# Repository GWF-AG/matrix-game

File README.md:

# Matrix-Game

Copyright (C) 2025 GWF AG, Obergrundstrasse 119, 6002 Lucerne, Switzerland

Contact: info@gwf.ch

## Trial Apprenticeship

This PCB is used as part of the trial apprenticeship for electronics/firmware at GWF AG in Lucerne.

_Deutsch: Schnupperlehre Elektroniker/in EFZ_

## Project

The project is used to practice soldering, measuring and potentially some coding.

The firmware currently supports the following games:
- [x] Snake
- [x] Tic-Tac-Toe
- [x] Drawing
- [x] Bomb Dodging
- [ ] Breakout

Feel free to submit a Pull Request to add more games! :tada:

## Changelogs

The changelogs can be find in the corresponding subdirectories:
- [Firmware Changelog](firmware/CHANGELOG.md)
- [Hardware Changelog](hardware/CHANGELOG.md)

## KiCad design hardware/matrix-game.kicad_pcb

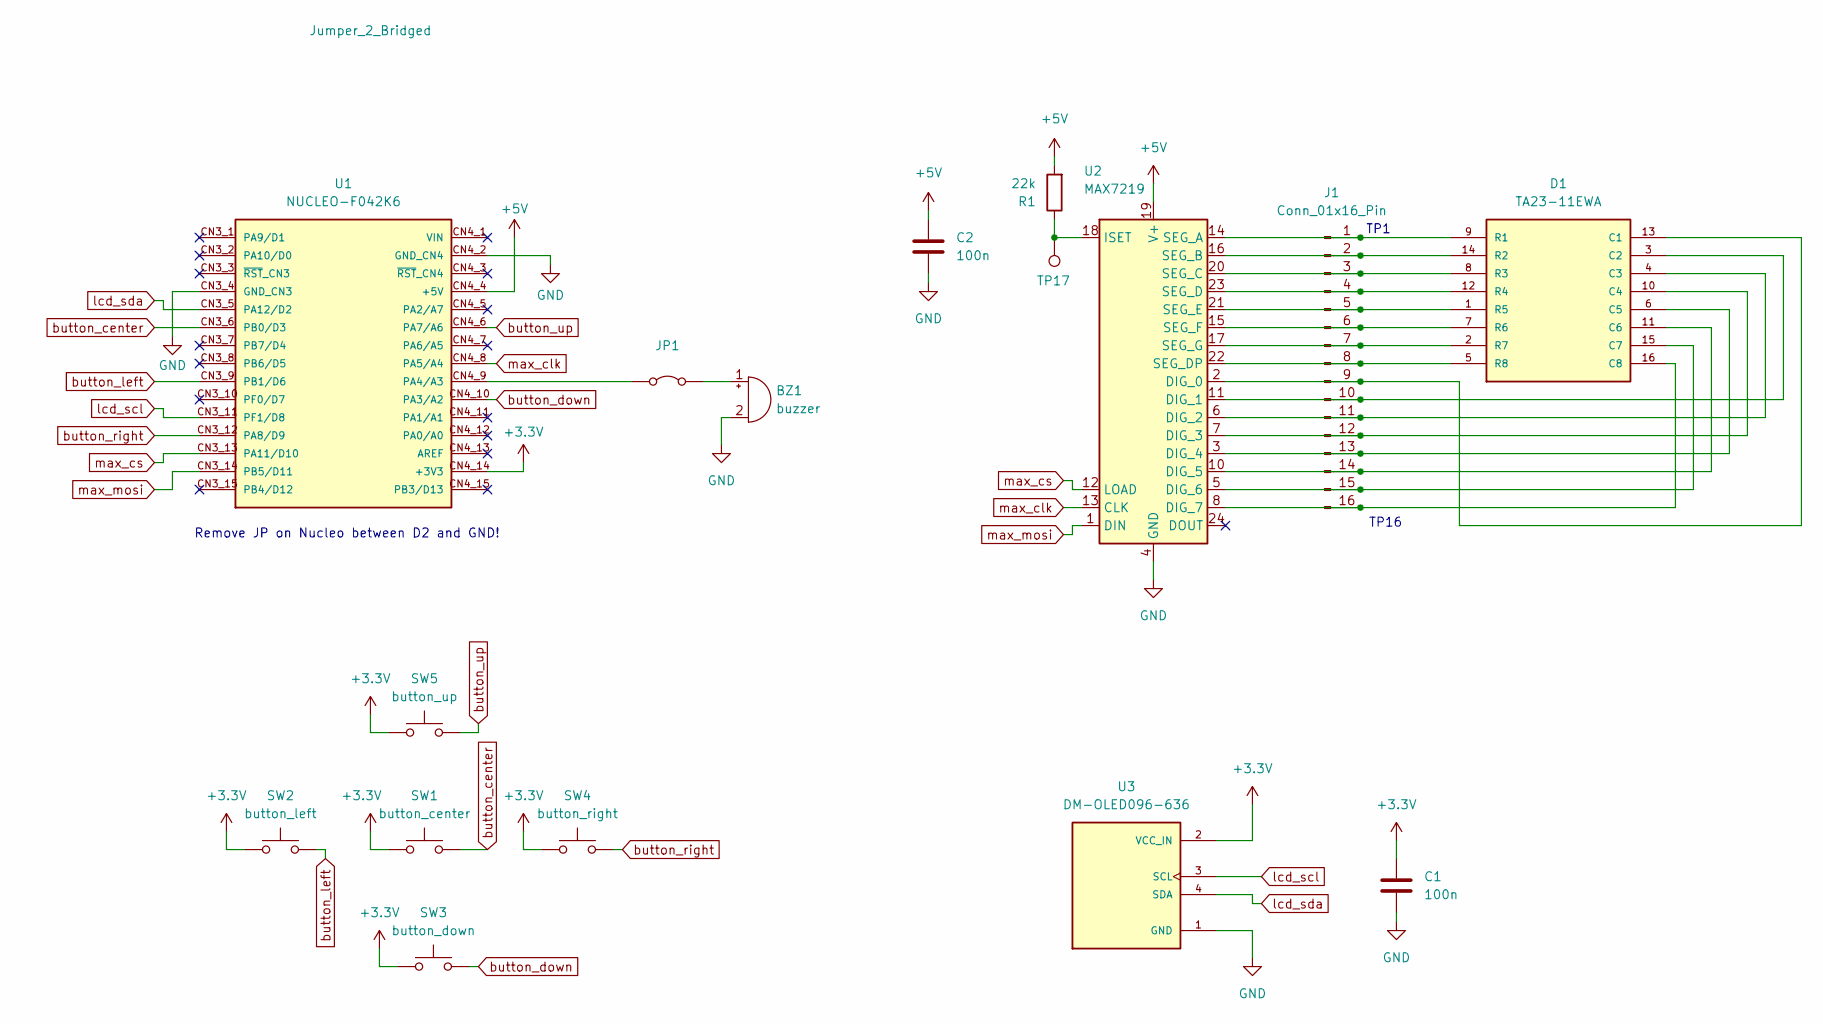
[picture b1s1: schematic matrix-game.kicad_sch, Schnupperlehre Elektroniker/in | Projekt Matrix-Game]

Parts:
BZ1: buzzer; Buzzer_12x9.5RM7.6
C1, C2: 100n; C_Disc_D3.0mm_W2.0mm_P2.50mm
D1: TA23-11EWA; LED_TA23-11EWA; PARTREV V.10A
J1: Conn_01x16_Pin; PinHeader_1x16_P2.54mm_Vertical
JP1: Jumper_2_Bridged; PinHeader_1x02_P2.54mm_Vertical
R1: 22k; R_Axial_DIN0207_L6.3mm_D2.5mm_P10.16mm_Horizontal
SW1: button_center; SW_PUSH_6mm
SW2: button_left; SW_PUSH_6mm
SW3: button_down; SW_PUSH_6mm
SW4: button_right; SW_PUSH_6mm
SW5: button_up; SW_PUSH_6mm
TP17: TestPoint; PinHeader_1x01_P2.54mm_Vertical
U1: NUCLEO-F042K6; MODULE_NUCLEO-F042K6; PARTREV 8
U2: MAX7219; DIP-24_W7.62mm_Socket
U3: DM-OLED096-636; MODULE_DM-OLED096-636; PARTREV 2018-09-10

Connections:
+3.3V: C1.1, SW1.1, SW2.1, SW3.1, SW4.1, SW5.1, U1.CN4_14 (+3V3), U3.2 (VCC_IN)
+5V: C2.1, R1.2, U1.CN4_4 (+5V), U2.19 (V+)
GND: BZ1.2 (-), C1.2, C2.2, U1.CN3_4 (GND_CN3), U1.CN4_2 (GND_CN4), U2.4 (GND), U2.9 (GND), U3.1 (GND)
unnamed: BZ1.1 (+), JP1.2 (B)
unnamed: D1.13 (C1), J1.9, U2.2 (DIG_0)
unnamed: D1.3 (C2), J1.10, U2.11 (DIG_1)
unnamed: D1.4 (C3), J1.11, U2.6 (DIG_2)
unnamed: D1.10 (C4), J1.12, U2.7 (DIG_3)
unnamed: D1.6 (C5), J1.13, U2.3 (DIG_4)
unnamed: D1.11 (C6), J1.14, U2.10 (DIG_5)
unnamed: D1.15 (C7), J1.15, U2.5 (DIG_6)
unnamed: D1.16 (C8), J1.16, U2.8 (DIG_7)
unnamed: D1.9 (R1), J1.1, U2.14 (SEG_A)
unnamed: D1.14 (R2), J1.2, U2.16 (SEG_B)
unnamed: D1.8 (R3), J1.3, U2.20 (SEG_C)
unnamed: D1.12 (R4), J1.4, U2.23 (SEG_D)
unnamed: D1.1 (R5), J1.5, U2.21 (SEG_E)
unnamed: D1.7 (R6), J1.6, U2.15 (SEG_F)
unnamed: D1.2 (R7), J1.7, U2.17 (SEG_G)
unnamed: D1.5 (R8), J1.8, U2.22 (SEG_DP)
unnamed: JP1.1 (A), U1.CN4_9 (PA4/A3)
unnamed: R1.1, TP17.1, U2.18 (ISET)
button_center: SW1.2, U1.CN3_6 (PB0/D3)
button_down: SW3.2, U1.CN4_10 (PA3/A2)
button_left: SW2.2, U1.CN3_9 (PB1/D6)
button_right: SW4.2, U1.CN3_12 (PA8/D9)
button_up: SW5.2, U1.CN4_6 (PA7/A6)
lcd_scl: U1.CN3_11 (PF1/D8), U3.3 (SCL)
lcd_sda: U1.CN3_5 (PA12/D2), U3.4 (SDA)
max_clk: U1.CN4_8 (PA5/A4), U2.13 (CLK)
max_cs: U1.CN3_13 (PA11/D10), U2.12 (LOAD)
max_mosi: U1.CN3_14 (PB5/D11), U2.1 (DIN)

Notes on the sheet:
TP16
TP1
Remove JP on Nucleo between D2 and GND!

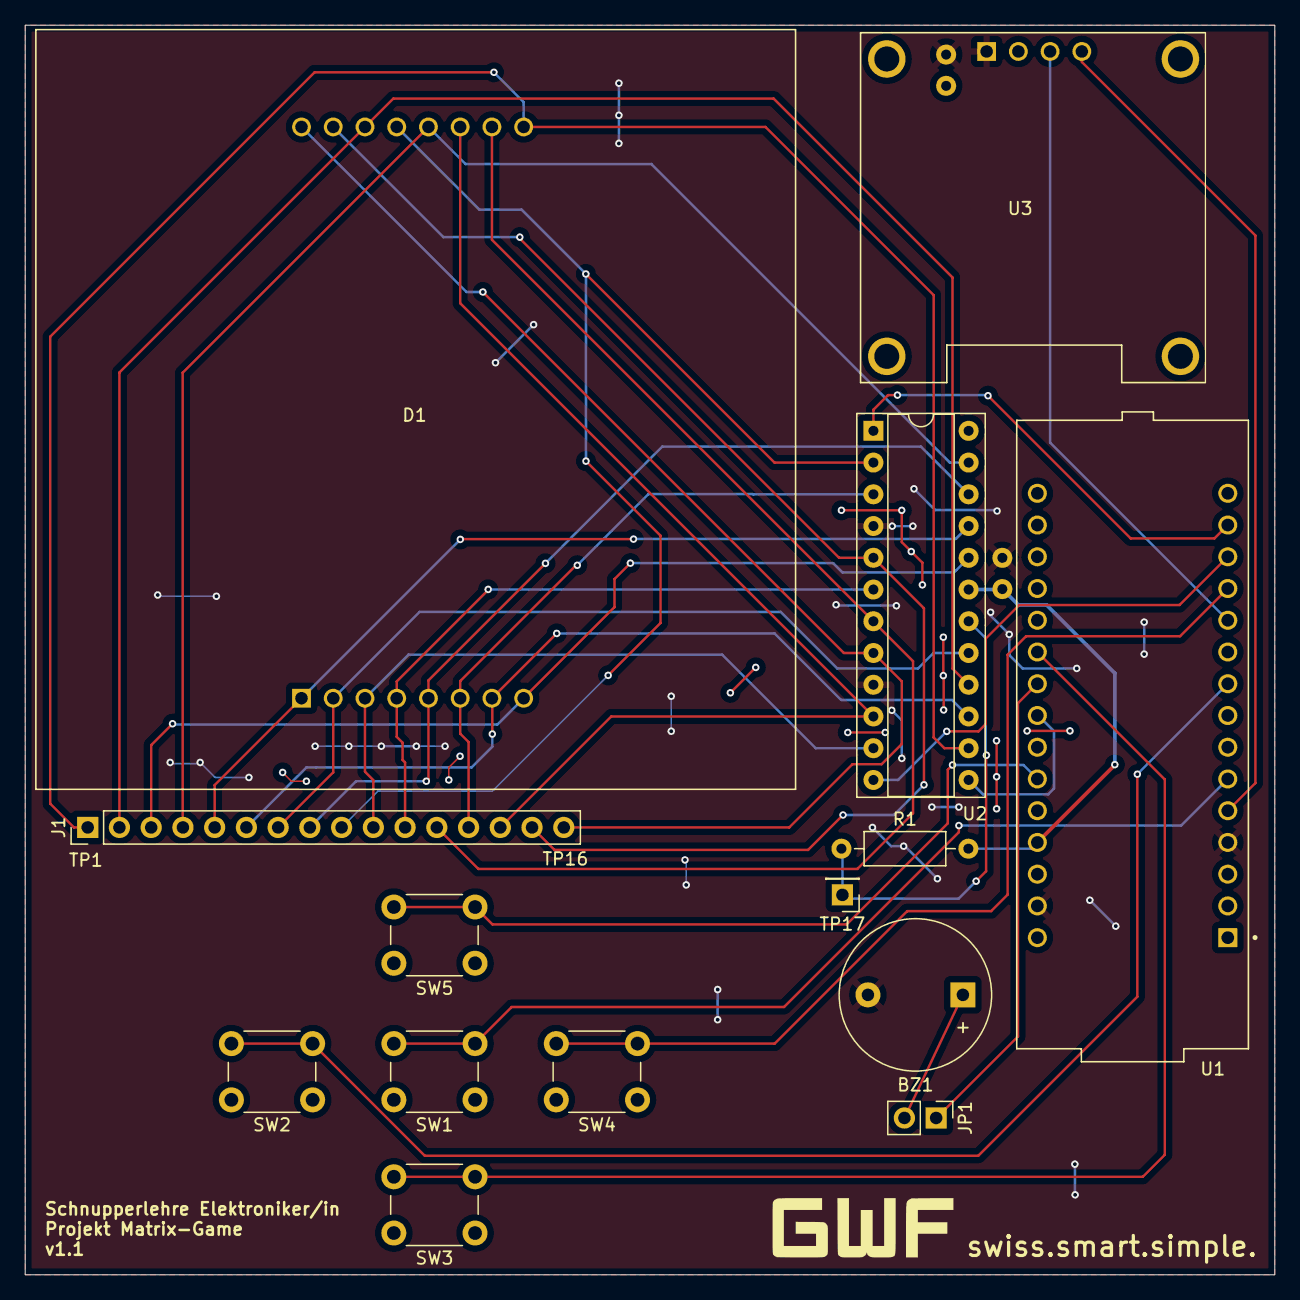
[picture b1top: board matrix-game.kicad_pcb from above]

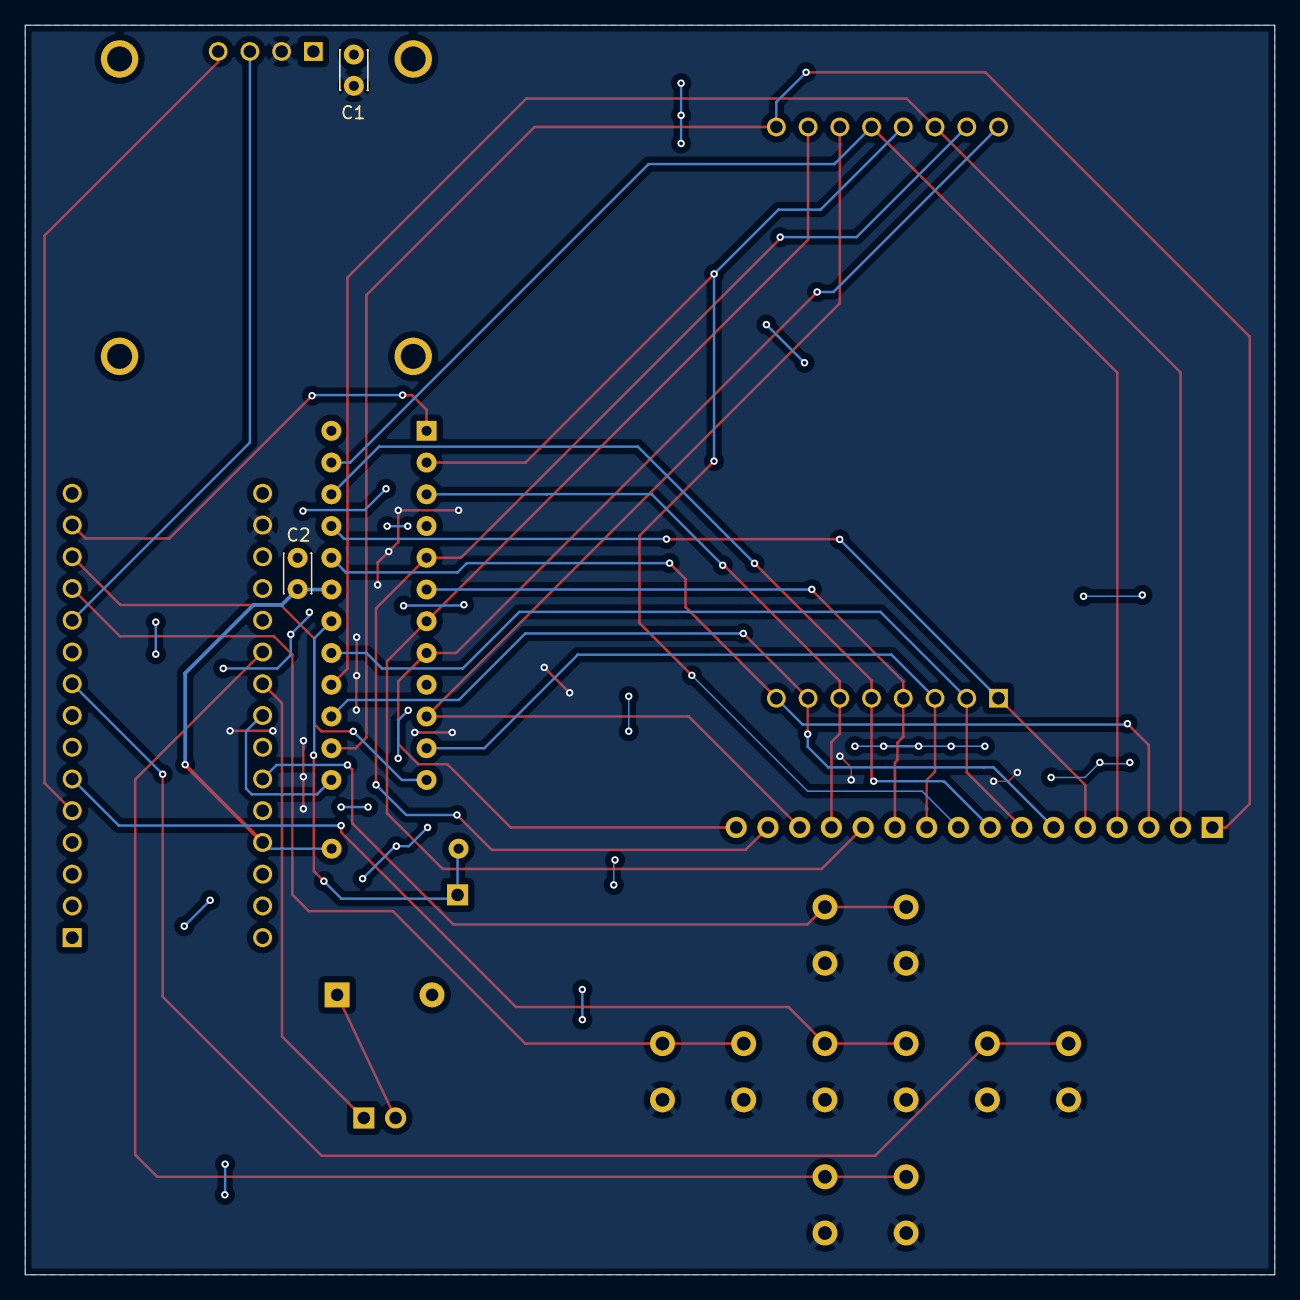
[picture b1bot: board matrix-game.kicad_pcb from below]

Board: 2 copper layers, 100.0 x 100.0 mm, 16 parts (2 on the bottom side), 32 nets.

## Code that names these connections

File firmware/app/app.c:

/**
 * @file app.c
 * @author Timon Burkard (timon.burkard@gwf.ch)
 *
 * @copyright Copyright (c) 2025 GWF AG
 *
 */

#include "app.h"

#include <stdbool.h>
#include <stdlib.h>
#include <stdio.h>

#include "main.h"
#include "max7219.h"
#include "tictactoe.h"
#include "snake.h"
#include "ball_catcher.h"
#include "ssd1306.h"

#define BUTTON_DEBOUNCE_DELAY_MS 10

#define GAME_OPTIONS_PER_SCREEN 3

extern SPI_HandleTypeDef hspi1;

typedef enum {
    SNAKE        = 0,
    TICTACTOE    = 1,
    BALL_CATCHER = 2,
    GAME_AMOUNT, // Keep at end!
} game_id_t;

typedef struct {
    game_id_t   id;
    const char* name;
    void (*run)(void);
} game_t;

/* clang-format off */

static game_t games[] = {
    [SNAKE]        = { .id = SNAKE,        .name = "Snake",        .run = snake        },
    [TICTACTOE]    = { .id = TICTACTOE,    .name = "TicTacToe",    .run = tictactoe    },
    [BALL_CATCHER] = { .id = BALL_CATCHER, .name = "Ball Catcher", .run = ball_catcher },
};

/* clang-format on */

bool      matrix[MAX7219_COLUMN_AMOUNT][MAX7219_ROW_AMOUNT] = { false };
max7219_t max7219                                           = { 0 };

void app_matrix_clean(bool matrix[MAX7219_COLUMN_AMOUNT][MAX7219_ROW_AMOUNT])
{
    for (uint8_t i = 0; i < MAX7219_COLUMN_AMOUNT; i++) {
        for (uint8_t j = 0; j < MAX7219_ROW_AMOUNT; j++) {
            matrix[i][j] = false;
        }
    }
}

button_t app_get_user_input(void)
{
    static bool button_up_previous     = 0;
    static bool button_down_previous   = 0;
    static bool button_left_previous   = 0;
    static bool button_right_previous  = 0;
    static bool button_center_previous = 0;

    button_t button = BUTTON_NONE;

    bool button_up_current     = HAL_GPIO_ReadPin(BUTTON_UP_GPIO_Port, BUTTON_UP_Pin);
    bool button_down_current   = HAL_GPIO_ReadPin(BUTTON_DOWN_GPIO_Port, BUTTON_DOWN_Pin);
    bool button_left_current   = HAL_GPIO_ReadPin(BUTTON_LEFT_GPIO_Port, BUTTON_LEFT_Pin);
    bool button_right_current  = HAL_GPIO_ReadPin(BUTTON_RIGHT_GPIO_Port, BUTTON_RIGHT_Pin);
    bool button_center_current = HAL_GPIO_ReadPin(BUTTON_CENTER_GPIO_Port, BUTTON_CENTER_Pin);

    if (button_up_current && !button_up_previous) {
        button = BUTTON_UP;
    }

    if (button_down_current && !button_down_previous) {
        button = BUTTON_DOWN;
    }

    if (button_left_current && !button_left_previous) {
        button = BUTTON_LEFT;
    }

    if (button_right_current && !button_right_previous) {
        button = BUTTON_RIGHT;
    }

    if (button_center_current && !button_center_previous) {
        button = BUTTON_CENTER;
    }

    button_up_previous     = button_up_current;
    button_down_previous   = button_down_current;
    button_left_previous   = button_left_current;
    button_right_previous  = button_right_current;
    button_center_previous = button_center_current;

    HAL_Delay(BUTTON_DEBOUNCE_DELAY_MS);

    return button;
}

void app_beep(uint16_t duration_ms)
{
    HAL_GPIO_WritePin(BUZZER_GPIO_Port, BUZZER_Pin, GPIO_PIN_SET);
    HAL_Delay(duration_ms);
    HAL_GPIO_WritePin(BUZZER_GPIO_Port, BUZZER_Pin, GPIO_PIN_RESET);
}

void app_lcd_print_title(void)
{
    SSD1306_Clear();
    SSD1306_GotoXY(0, APP_LCD_ROW_TITLE);
    SSD1306_Puts(APP_LCD_TITLE, &Font_7x10, 1);
    SSD1306_GotoXY(0, APP_LCD_ROW_TITLE_SEPARATION);
    SSD1306_Puts(APP_LCD_TITLE_SEPARATION, &Font_7x10, 1);
    SSD1306_UpdateScreen();
}

static void lcd_print_game_selection(game_id_t game_id)
{
    // Clear all game options
    SSD1306_GotoXY(0, APP_LCD_ROW_GAME_NAME);
    SSD1306_Puts(APP_LCD_EMPTY_LINE, &Font_7x10, 1);
    SSD1306_GotoXY(0, APP_LCD_ROW_GAME_DYNAMIC_0);
    SSD1306_Puts(APP_LCD_EMPTY_LINE, &Font_7x10, 1);
    SSD1306_GotoXY(0, APP_LCD_ROW_GAME_DYNAMIC_1);
    SSD1306_Puts(APP_LCD_EMPTY_LINE, &Font_7x10, 1);

    game_id_t        start_id          = 0;
    static game_id_t start_id_previous = 0;

    // Check if currently selected game is still displayable with the previous start ID
    if ((start_id_previous <= game_id) && (game_id < (start_id_previous + GAME_OPTIONS_PER_SCREEN))) {
        start_id = start_id_previous;
    } else if (game_id < start_id_previous) {
        start_id = game_id;
    } else if (game_id >= (start_id_previous + GAME_OPTIONS_PER_SCREEN)) {
        start_id = game_id - (GAME_OPTIONS_PER_SCREEN - 1);
    }

    for (uint8_t i = 0; i < GAME_OPTIONS_PER_SCREEN; i++) {
        if ((start_id + i) >= GAME_AMOUNT) {
            break;
        }

        if ((start_id + i) == game_id) {
            SSD1306_GotoXY(0, APP_LCD_ROW_GAME_NAME + (i * APP_LCD_ROW_GAME_DIFFERENCE));
            SSD1306_Puts(">", &Font_7x10, 1);
        }

        SSD1306_GotoXY(APP_LCD_COL_GAME_SELECTION_INDENTATION, APP_LCD_ROW_GAME_NAME + (i * APP_LCD_ROW_GAME_DIFFERENCE));
        SSD1306_Puts(games[start_id + i].name, &Font_7x10, 1);
    }

    SSD1306_UpdateScreen();

    start_id_previous = start_id;
}

static game_id_t select_game(void)
{
    button_t         button  = BUTTON_NONE;
    static game_id_t game_id = SNAKE;

    app_lcd_print_title();

    lcd_print_game_selection(game_id);

    do {
        do {
            button = app_get_user_input();
        } while (button == BUTTON_NONE);

        if (button == BUTTON_DOWN) {
            if (game_id < (GAME_AMOUNT - 1)) {
                ++game_id;
            }

            lcd_print_game_selection(game_id);
        }

        if (button == BUTTON_UP) {
            if (game_id > 0) {
                --game_id;
            }

            lcd_print_game_selection(game_id);
        }
    } while (button != BUTTON_CENTER);

    return game_id;
}

void app(void)
{
    game_id_t game_id;

    if (max7219_init(&max7219, &hspi1, MAX_SPI_CS_GPIO_Port, MAX_SPI_CS_Pin) != MAX7219_OK) {
        for (;;) {
        } // Error handling...
    }

    SSD1306_Init();

    for (;;) {
        app_matrix_clean(matrix);

        if (max7219_set_matrix(&max7219, matrix) != MAX7219_OK) {
            for (;;) {
            } // Error handling...
        }

        game_id = select_game();

        if (games[game_id].run != NULL) {
            games[game_id].run();
        }
    }
}

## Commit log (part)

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2025-04-30 added structure for new ball-catcher game
2025-10-09 [firmware] bomb dodging fixed text output on LCD
2025-10-09 [firmware] BombDodger: fixed the name displayed on the LCD and randomized bomb spawn locations
2025-10-09 [firmware] BombDodger get rid of magic numbers
2025-10-09 [firmware] BombDodger refactoring: switched row to col
2025-10-09 [firmware/doc] updated changelog
2025-10-09 [firmware] BombDodger enable user to exit the game by pressing CENTER button
2025-10-09 [firmware] breakout: added wall/border collision and fixed some small bugs TBC
2025-10-09 [firmware] use local variables instead of global variables
    The logic is not yet perfect:
    - Not all dots can be removed
    - Paddle collision: Dots sometimes jump not so nicely (a bit too far)
2025-10-13 [firmware/games/minor] breakout: get rid of magic number
2025-10-13 [firmware/games] breakout: lets speed it up a bit
2025-12-10 [firmware/docs] update README
